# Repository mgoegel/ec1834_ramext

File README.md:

# EC1834 RAM Erweiterung - entfesselt

Ich dokumentiere hier die 384kb RAM Speicherweiterung des Robotron EC1834
im Rahmen meines Troubleshootings an 2 defekten Boards.

Dies ist die Digitalisierung des originalen Schaltplans.
Ich habe vorhandene Fehler gefixt, dafür aber möglicherweise neue eingebaut... ;-)

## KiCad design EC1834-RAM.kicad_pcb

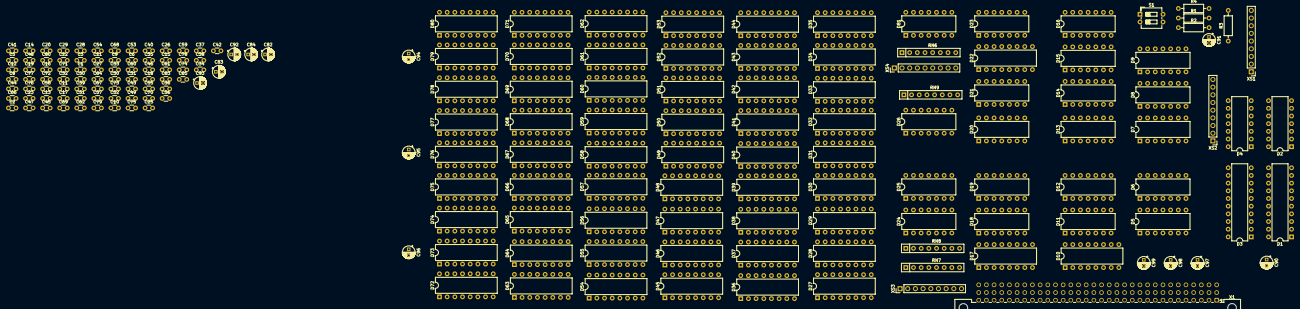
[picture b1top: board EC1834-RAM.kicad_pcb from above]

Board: 2 copper layers, 185 parts (0 on the bottom side), 23 nets, no tracks yet.

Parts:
C1, C2, C3, C5, C6, C8, C9, C10, C11, C12, C13, C14, C15, C16, C17, C18, C19, C20, C21, C22, C23, C25, C26, C27, C28, C29, C30, C31, C32, C33, C34, C35, C36, C37, C38, C39, C40, C41, C42, C43, C44, C45, C46, C47, C48, C49, C50, C51, C52, C53, C54, C55, C56, C57, C58, C59, C60, C61, C62, C63, C64, C65, C66, C67, C68, C69, C70, C71, C72, C73, C74, C75, C76, C77, C78, C79, C80: 100n; C_Disc_D3.0mm_W1.6mm_P2.50mm
C82, C83, C84, C90, C91, C92, C93, C94, C95, C96, C97, C98, C99: 47uF; CP_Radial_D4.0mm_P2.00mm
D1, D3: DS8287D; DIP-20_W7.62mm
D2, D4: 74LS280; DIP-14_W7.62mm
D5, D11: DL030D; DIP-14_W7.62mm
D6, D14, D15, D16: DL074; DIP-14_W7.62mm
D7: 74S64; DIP-14_W7.62mm
D8, D26: DL008D; DIP-14_W7.62mm
D9: DL086D; DIP-14_W7.62mm
D10, D17: 74LS257; DIP-16_W7.62mm
D12, D18, D21: DL004D; DIP-14_W7.62mm
D13: DL002D; DIP-14_W7.62mm
D19: DL032D; DIP-14_W7.62mm
D20: DL051D; DIP-14_W7.62mm
D22: DS8205; DIP-16_W7.62mm
D23, D25, D81: DL000D; DIP-14_W7.62mm
D24: DL003D; DIP-14_W7.62mm
D27, D28, D29, D30, D31, D32, D33, D34, D35, D36, D37, D38, D39, D40, D41, D42, D43, D44, D45, D46, D47, D48, D49, D50, D51, D52, D53, D54, D55, D56, D57, D58, D59, D60, D61, D62, D63, D64, D65, D66, D67, D68, D69, D70, D71, D72, D73, D74, D75, D76, D77, D78, D79, D80: U2164; DIP-16_W7.62mm
R1, R2, R4: 1k; R_Axial_DIN0207_L6.3mm_D2.5mm_P10.16mm_Horizontal
R3: 80; R_Axial_DIN0207_L6.3mm_D2.5mm_P10.16mm_Horizontal
RN6, RN7, RN8, RN9: 30; R_Array_SIP8
S1: SW_DIP_x02; SW_DIP_SPSTx02_Slide_6.7x6.64mm_W7.62mm_P2.54mm_LowProfile
X1: BUS_EC1834_16Bit_RAMCAR; DIN41612_C_3x32_Male_Horizontal_THT
XS1, XS2, XS3, XS4: Conn_01x09; PinHeader_1x09_P2.54mm_Vertical

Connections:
+5V: C1.1, C2.1, C3.1, C5.1, C6.1, C8.1, C9.1, C10.1, C11.1, C12.1, C13.1, C14.1, C15.1, C16.1, C17.1, C18.1, C19.1, C20.1, C21.1, C22.1, C23.1, C25.1, C26.1, C27.1, C28.1, C29.1, C30.1, C31.1, C32.1, C33.1, C34.1, C35.1, C36.1, C37.1, C38.1, C39.1, C40.1, C41.1, C42.1, C43.1, C44.1, C45.1, C46.1, C47.1, C48.1, C49.1, C50.1, C51.1, C52.1, C53.1, C54.1, C55.1, C56.1, C57.1, C58.1, C59.1, C60.1, C61.1, C62.1, C63.1, C64.1, C65.1, C66.1, C67.1, C68.1, C69.1, C70.1, C71.1, C72.1, C73.1, C74.1, C75.1, C76.1, C77.1, C78.1, C79.1, C80.1, C90.1, C91.1, C92.1, C93.1, C94.1, C95.1, C96.1, D1.20 (Vcc), D2.14 (VCC), D3.20 (Vcc), D4.14 (VCC), D5.14 (Vcc), D6.14 (VCC), D7.14 (VCC), D8.14 (Vcc), D9.14 (Vcc), D10.16 (VCC), D12.14 (Vcc), D13.14 (Vcc), D14.14 (VCC), D15.14 (VCC), D16.14 (VCC), D17.16 (VCC), D18.14 (Vcc), D19.14 (Vcc), D20.14 (Vcc), D21.14 (Vcc), D22.16 (VCC), D23.14 (Vcc), D24.14 (Vcc), D25.14 (Vcc), D26.14 (Vcc), D81.14 (Vcc)
+12V: C83.1, C99.1
-5V: C84.1, C97.1
-12V: C82.1, C98.1
/Control/MA6: RN7.1 (R1.1), XS3.2
/Control/MA7: RN8.1 (R1.1), XS3.1
/Control/XS1_9: D7.2, D7.3, D7.9, D7.10, R3.1, XS1.9
/Control/~CASH: RN9.1 (R1.1), XS4.2
/Control/~CASL: RN9.3 (R2.1), XS4.4
GND: C1.2, C2.2, C3.2, C5.2, C6.2, C8.2, C9.2, C10.2, C11.2, C12.2, C13.2, C14.2, C15.2, C16.2, C17.2, C18.2, C19.2, C20.2, C21.2, C22.2, C23.2, C25.2, C26.2, C27.2, C28.2, C29.2, C30.2, C31.2, C32.2, C33.2, C34.2, C35.2, C36.2, C37.2, C38.2, C39.2, C40.2, C41.2, C42.2, C43.2, C44.2, C45.2, C46.2, C47.2, C48.2, C49.2, C50.2, C51.2, C52.2, C53.2, C54.2, C55.2, C56.2, C57.2, C58.2, C59.2, C60.2, C61.2, C62.2, C63.2, C64.2, C65.2, C66.2, C67.2, C68.2, C69.2, C70.2, C71.2, C72.2, C73.2, C74.2, C75.2, C76.2, C77.2, C78.2, C79.2, C80.2, C82.2, C83.2, C84.2, C90.2, C91.2, C92.2, C93.2, C94.2, C95.2, C96.2, C97.2, C98.2, C99.2, D1.10 (GND), D2.7 (GND), D3.10 (GND), D4.7 (GND), D5.7 (GND), D6.7 (GND), D7.7 (GND), D8.7 (GND), D9.7 (GND), D9.12 (A4), D9.13 (B4), D10.8 (GND), D12.7 (GND), D12.13 (A6), D13.7 (GND), D14.7 (GND), D14.10 (S), D14.11 (C), D14.12 (D), D14.13 (R), D15.7 (GND), D16.7 (GND), D17.8 (GND), D18.7 (GND), D19.7 (GND), D19.9 (A3), D19.10 (B3), D19.12 (A4), D19.13 (B4), D20.7 (GND), D21.7 (GND), D21.9 (A4), D22.8 (GND), D23.7 (GND), D24.1 (A1), D24.2 (B1), D24.4 (A2), D24.5 (B2), D24.7 (GND), D25.1 (A1), D25.2 (B1), D25.7 (GND), D26.7 (GND), D81.7 (GND), D81.12 (A4), D81.13 (B4)
unnamed: D10.12 (F3), RN8.4 (R2.2)
unnamed: D17.4 (F0), RN7.8 (R4.2)
unnamed: D17.7 (F1), RN7.5 (R3.1)
unnamed: D17.9 (F2), RN8.6 (R3.2)
unnamed: D17.12 (F3), RN8.7 (R4.1)
unnamed: D25.8 (Y3), RN9.4 (R2.2)
unnamed: D25.11 (Y4), RN9.2 (R1.2)
unnamed: D81.3 (Y1), RN6.4 (R2.2)
unnamed: D81.8 (Y3), RN6.2 (R1.2)
unnamed: D81.6 (Y2), RN6.6 (R3.2)
unnamed: D10.9 (F2), RN7.2 (R1.2)
unnamed: D10.4 (F0), RN7.4 (R2.2)
unnamed: D10.7 (F1), RN8.2 (R1.2)
